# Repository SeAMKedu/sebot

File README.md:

# SeBot

SeBot-robotin ROS2 ohjelmointiohjeet 28.5.2025 OpenUGV-hankkeen ROS2 mobiilirobotti-työpajaan.

Varsinaiset ohjeet on kirjoitettu markdown-tiedostoihin. Niiden mukaiset valmiit koodit (ROS2, Arduino ja WWW) löydät repositorion code-kansiosta.

SeBotia varten on olemassa Rasberry Pi 5:lle sopiva image-tiedosto, jonka voi kirjoittaa MicroSD-muistikortille. Image sisältää valmiin ROS2 ympäristön ja muut tämän harjoituksen kannalta tarpeelliset muut tiedostot ja ohjelmat. Tiedosto on talletettu OpenUGV-hankkeen Teams-ryhmään (vaatii käyttöoikeuden SeAMK:lta). Mikäli sinulla ei ole käytössä tätä image-tiedostoa tai haluat tehdä harjoituksen jollain muulla koneella, voit hyvin asentaa ROS2-ympäristön itse ``apt install``-komennolla Ubuntun pakettijakelun kautta. Ohje tähän löytyy Materiaali 0:sta.

Jos haluat tulostaa oman SeBot-pohjan, STP-malli ja PDF-mittakuva löytyy SeBot-kansiosta. Huomaa kuitenkin, että tämän harjoituksen kannalta pohjalevyn muoto on hyvin vapaa ja robotin voi rakentaa vaikkapa riittävän tukevaan muovirasiaan.

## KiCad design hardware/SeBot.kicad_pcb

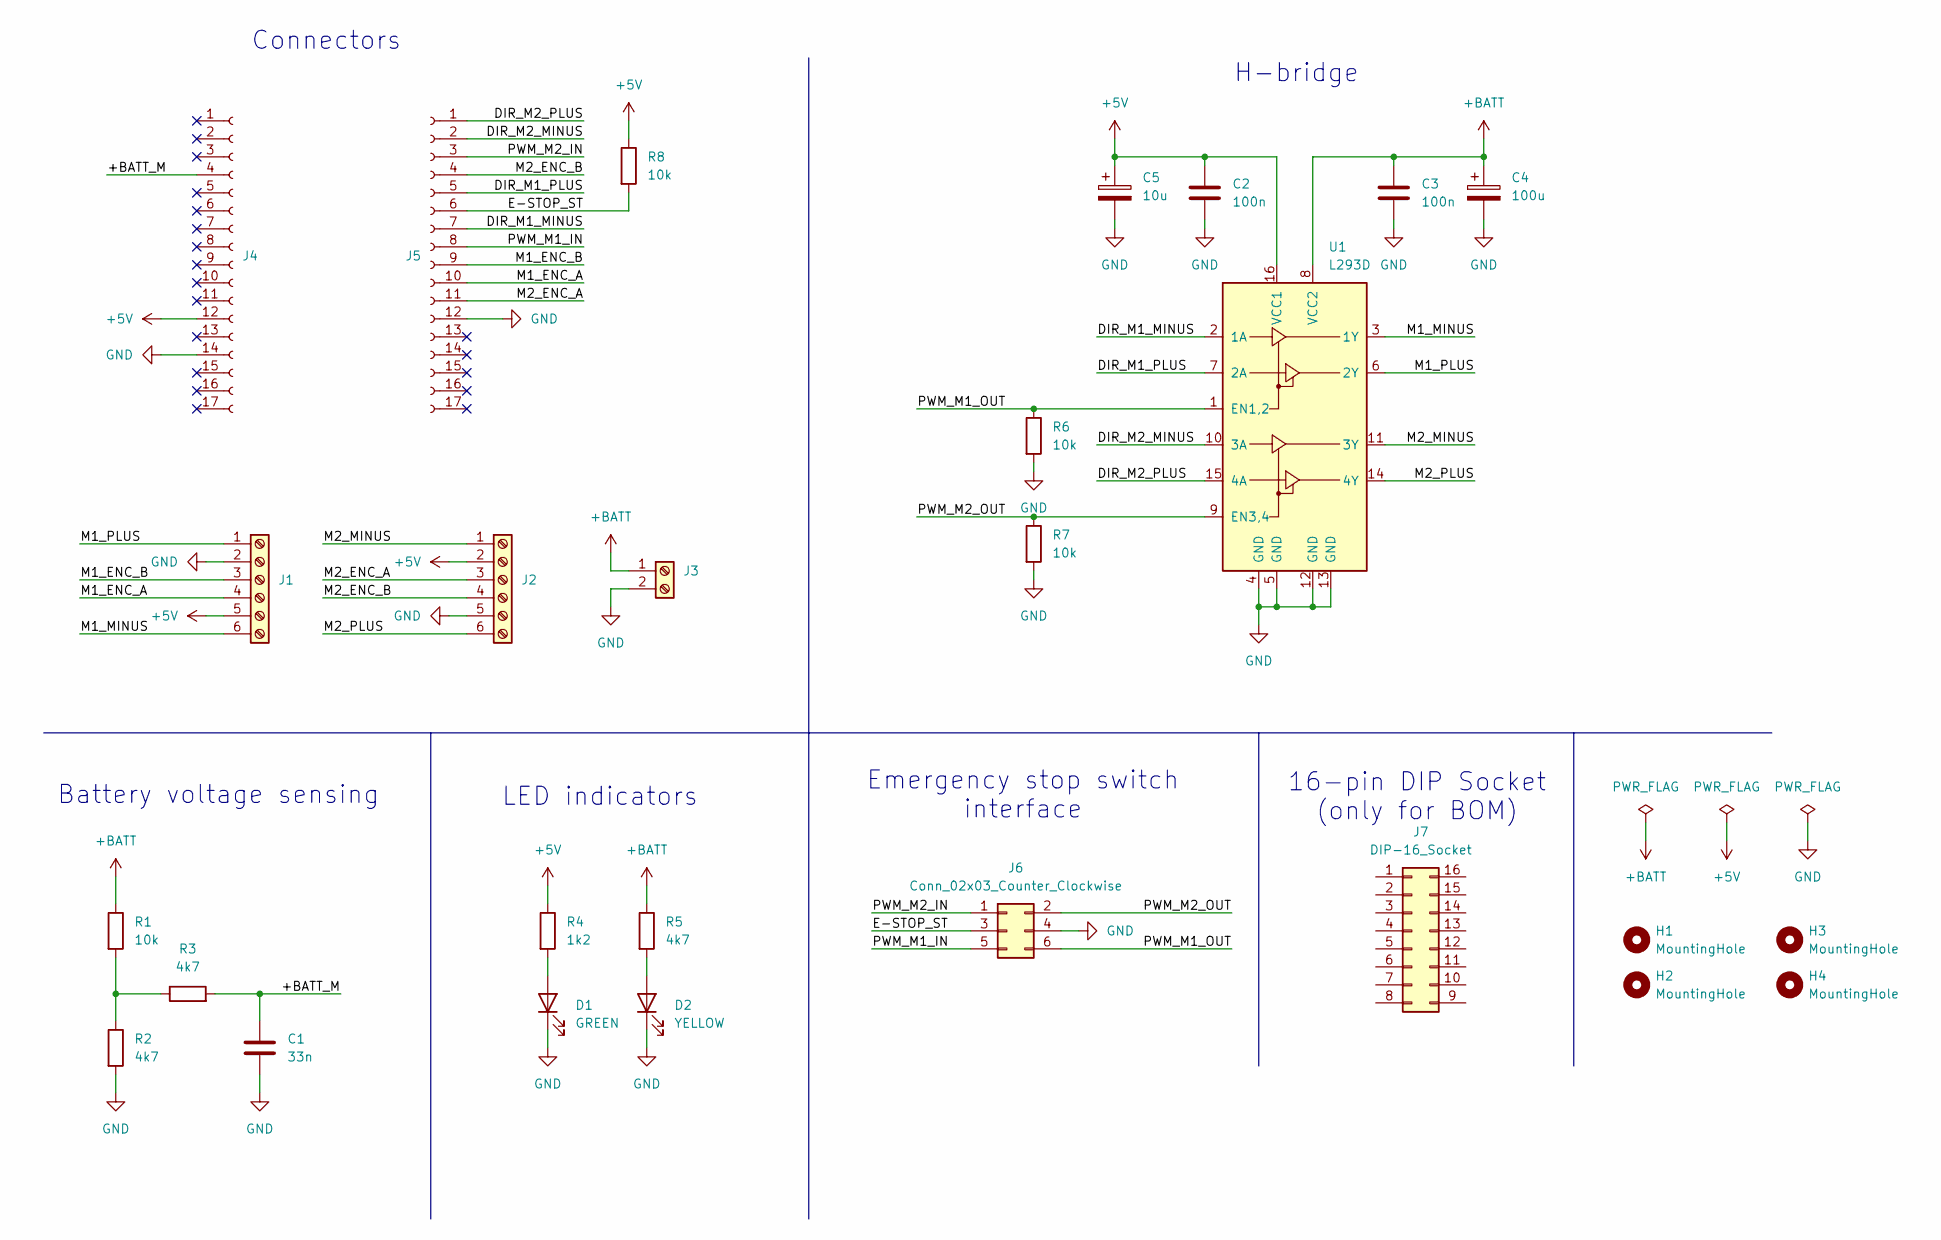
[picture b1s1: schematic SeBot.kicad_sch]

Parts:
C1: 33n; C_Disc_D3.8mm_W2.6mm_P2.50mm; Manufacturer Part No. K333K15X7RF5TL2; Farnell Part No. 3812207
C2, C3: 100n; C_Disc_D3.8mm_W2.6mm_P2.50mm; Manufacturer Part No. K104K15X7RF5TL2; Farnell Part No. 2860097
C4: 100u; CP_Radial_D6.3mm_P2.50mm; Manufacturer Part No. ECA1VM101; Farnell Part No. 9693670
C5: 10u; CP_Radial_D5.0mm_P2.00mm; Manufacturer Part No. ECA1JM100; Farnell Part No. 9693831
D1: GREEN; LED_D5.0mm; Manufacturer Part No. N/A; Farnell Part No. N/A
D2: YELLOW; LED_D5.0mm; Manufacturer Part No. N/A; Farnell Part No. N/A
H1, H2, H3, H4: MountingHole; MountingHole_3mm
J1, J2: Screw_Terminal_01x06; TerminalBlock_Phoenix_MKDSN-1,5-6-5.08_1x06_P5.08mm_Horizon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; Manufacturer Part No. 1729160; Farnell Part No. 3041499
J3: Screw_Terminal_01x02; TerminalBlock_Phoenix_MKDSN-1,5-2-5.08_1x02_P5.08mm_Horizon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; Manufacturer Part No. 1729128; Farnell Part No. 3041440
J4, J5: Conn_01x17_Socket; PinSocket_1x17_P2.54mm_Vertical; Manufacturer Part No. M20-7821746; Farnell Part No. 3755878
J6: Conn_02x03_Counter_Clockwise; PinHeader_2x03_P2.54mm_Vertical; Manufacturer Part No. 2213S-06G; Farnell Part No. 1593440
J7: DIP-16_Socket; Manufacturer Part No. 1-2199298-4; Farnell Part No. 1-2199298-4
R1, R6, R7, R8: 10k; R_Axial_DIN0207_L6.3mm_D2.5mm_P7.62mm_Horizontal; Manufacturer Part No. N/A; Farnell Part No. N/A
R2, R3, R5: 4k7; R_Axial_DIN0207_L6.3mm_D2.5mm_P7.62mm_Horizontal; Manufacturer Part No. N/A; Farnell Part No. N/A
R4: 1k2; R_Axial_DIN0207_L6.3mm_D2.5mm_P7.62mm_Horizontal; Manufacturer Part No. N/A; Farnell Part No. N/A
U1: L293D; DIP-16_W7.62mm_Socket; Manufacturer Part No. L293D; DigiKey Part No. 497-2936-5-ND

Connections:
+5V: C2.1, C5.1, J1.5, J2.2, J4.12, R4.1, R8.1, U1.16 (VCC1)
+BATT: C3.1, C4.1, J3.1, R1.1, R5.1, U1.8 (VCC2)
/+BATT_M: C1.1, J4.4, R3.2
/DIR_M1_MINUS: J5.7, U1.2 (1A)
/DIR_M1_PLUS: J5.5, U1.7 (2A)
/DIR_M2_MINUS: J5.2, U1.10 (3A)
/DIR_M2_PLUS: J5.1, U1.15 (4A)
/E-STOP_ST: J5.6, J6.3, R8.2
/M1_ENC_A: J1.4, J5.10
/M1_ENC_B: J1.3, J5.9
/M1_MINUS: J1.6, U1.3 (1Y)
/M1_PLUS: J1.1, U1.6 (2Y)
/M2_ENC_A: J2.3, J5.11
/M2_ENC_B: J2.4, J5.4
/M2_MINUS: J2.1, U1.11 (3Y)
/M2_PLUS: J2.6, U1.14 (4Y)
/PWM_M1_IN: J5.8, J6.5
/PWM_M1_OUT: J6.6, R6.1, U1.1 (EN1,2)
/PWM_M2_IN: J5.3, J6.1
/PWM_M2_OUT: J6.2, R7.1, U1.9 (EN3,4)
GND: C1.2, C2.2, C3.2, C4.2, C5.2, D1.1 (K), D2.1 (K), J1.2, J2.5, J3.2, J4.14, J5.12, J6.4, R2.2, R6.2, R7.2, U1.4 (GND), U1.5 (GND), U1.12 (GND), U1.13 (GND)
unnamed: D1.2 (A), R4.2
unnamed: D2.2 (A), R5.2
unnamed: R1.2, R2.1, R3.1

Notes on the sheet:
16-pin DIP Socket (only for BOM)
Battery voltage sensing
Connectors
Emergency stop switch interface
H-bridge
LED indicators

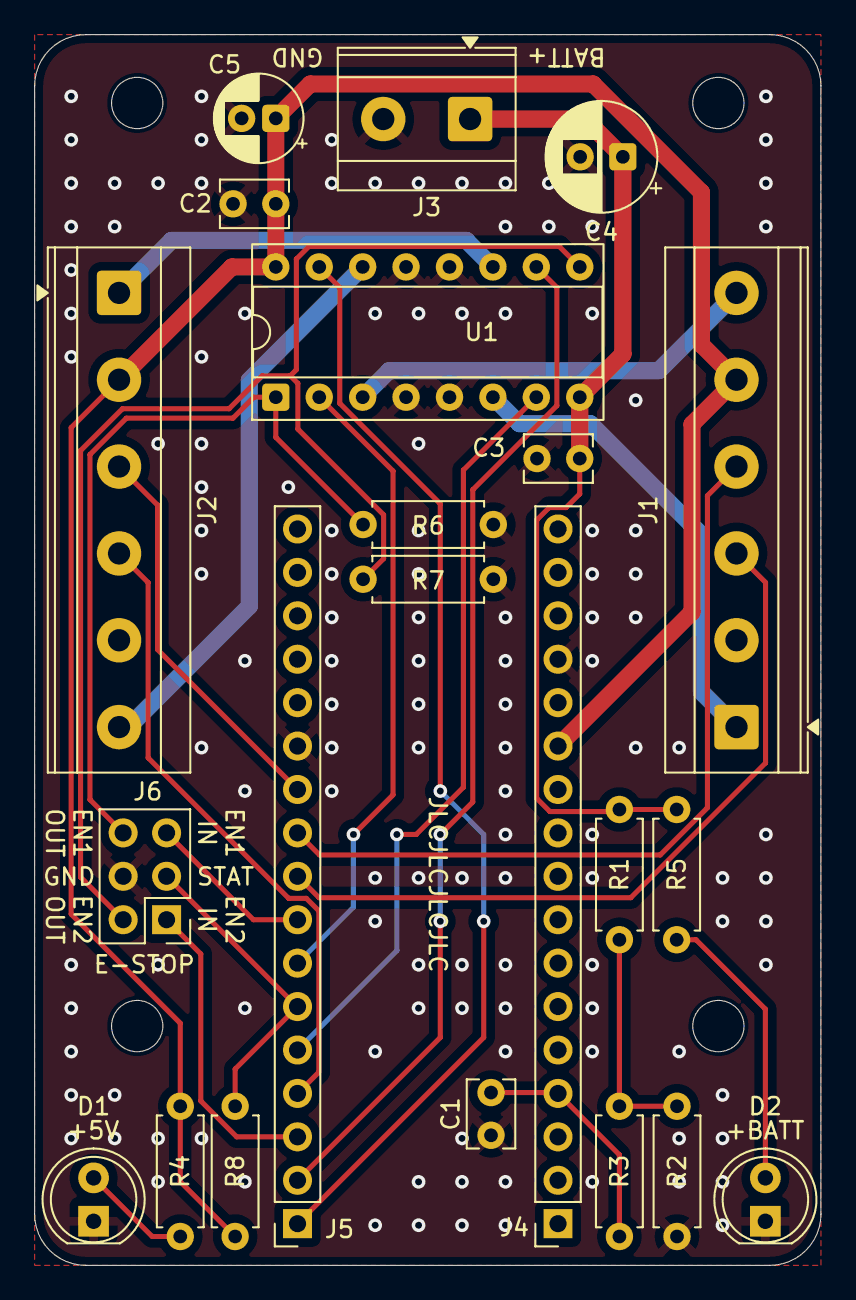
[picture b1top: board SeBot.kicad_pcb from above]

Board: 2 copper layers, 46.0 x 72.0 mm, 26 parts (0 on the bottom side), 24 nets.

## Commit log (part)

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2025-05-27 Alkuperäinen commit ensimmäisestä julkaisusta SeBotille.
2025-05-27 Lisätty tietoa readme.md:hen.
2025-05-27 Update materiaali-2-motordriver.md
    Muutettiin teksti kannustamaan namespacen sijaan ROS_DOMAIN_ID:n vaihtamiseen.
2025-05-27 Update materiaali-3-URDF.md
    Lisätty kommenttirivit namespace-lisäysten kohdille
2025-05-27 Update materiaali-4-diffdrive.md
    kommentoitu pois namespace-kohtia
2025-05-27 Update materiaali-4-diffdrive.md
    Tarkistuksia kirjoitusvirheisiin.
2025-05-27 Update materiaali-2-motordriver.md
    Kirjoitusvirheiden poistoa
2025-05-27 Kirjoitusvirheiden korjausta ja tekstin selkeyttämistä
2025-05-27 Kirjoitusvirheitä
2025-05-27 Kansikuvan vaihto
2025-05-28 Muokattiin diffdrive launch-fileä ja vietiin kaikki muutokset ros2_ws-koodeihin.
2025-05-28 ROS2 asennus, osalista, Foxglove
2025-05-28 Lisäykset
2025-05-30 SeBot alustan malli, lisäyksiä
2025-05-30 tarkennus akun jännitevaatimuksiin.
2025-06-05 Lisätty akun varauksen seuranta.
2025-06-05 Kuvan pienennys
2025-06-05 Muutettu ROS2_WS koodit tukemaan akun varauksen lukua.
2025-06-05 Arduinon koodin akun jänniteseurantaversiot
2025-06-05 battery paketin hakemiston korjaus
2025-06-05 Bugeja korjattu
2025-06-05 Päivitetty materiaali bugikorjauksien jäljiltä
2025-06-05 battery_alert
2025-06-05 tekstejä korjattu
2025-06-09 SeBot urdf
2025-11-03 Fix calculation of left and right wheel speeds
2025-11-03 Add ticks_per_revolution parameter to cmd_vel_node
2025-12-16 Add DOI badge to README
2025-12-16 Update README with SeBot programming instructions
    Added a brief introduction to SeBot and its programming instructions.
